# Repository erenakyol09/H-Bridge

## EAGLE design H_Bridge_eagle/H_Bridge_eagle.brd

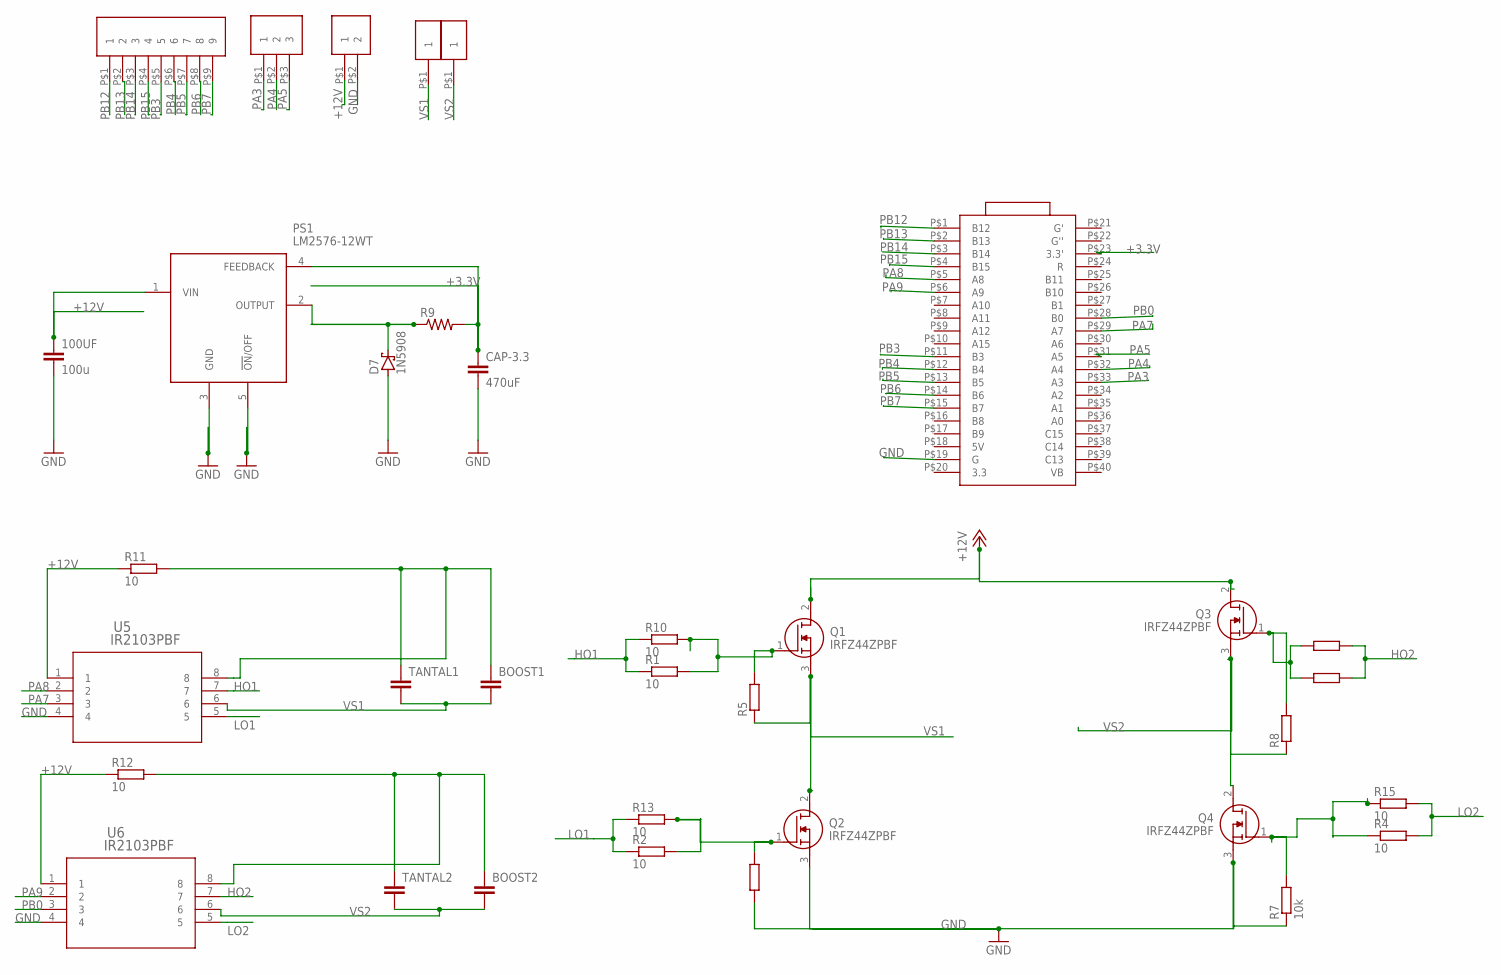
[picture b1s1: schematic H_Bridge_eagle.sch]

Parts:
100UF: 100u; C5B5
BOOST1, BOOST2: C-EU025-040X050; C025-040X050
CAP-3.3: 470uF; C050-075X075
D7: 1N5908; C4111-15
PS1: LM2576-12WT; TO170P470X1016X1900-5P
Q1, Q2, Q3, Q4: IRFZ44ZPBF; TO254P482X1016X2192-3P
R1, R2, R3, R4, R10, R11, R12, R13, R14, R15: 10; 0204/7
R5, R6, R7, R8: 10k; 0204/7
R9: R-US_VTA55; VTA55
TANTAL1, TANTAL2: C-EU025-024X044; C025-024X044
U5, U6: IR2103PBF; IC8_IR2103PBF_INF
U$1: BLUE_PILL_EA; BLUE_PILL_FOOT
U$2: HEADER_9; HEADER_9_FOOT
U$3: HEADER_3; HEADER_3_FOOT
U$4: HEADER_2; HEADER_2_FOOT
U$5, U$6: HEADER_1; HEADER_1_FOOT

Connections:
+3.3V: CAP-3.3.1, PS1.4 (FEEDBACK), R9.2, U$1.P$23 (3.3')
+12V: 100UF.1, PS1.1 (VIN), Q1.2 (D), Q3.2 (D), R11.1, R12.1, U5.1, U6.1, U$4.P$1 (1)
GND: 100UF.2, CAP-3.3.2, D7.A, PS1.3 (GND), PS1.5 (!ON!/OFF), Q2.3 (S), Q4.3 (S), R6.1, R7.1, U5.4, U6.4, U$1.P$19 (G), U$4.P$2 (2)
HO1: R1.1, R10.1, U5.7
HO2: R3.2, R14.2, U6.7
LO1: R2.1, R13.1, U5.5
LO2: R4.2, R15.2, U6.5
unnamed: BOOST2.1, R12.2, TANTAL2.1, U6.8
unnamed: BOOST1.1, R11.2, TANTAL1.1, U5.8
unnamed: D7.C, PS1.2 (OUTPUT), R9.1
unnamed: Q4.1 (G), R4.1, R7.2, R15.1
unnamed: Q3.1 (G), R3.1, R8.2, R14.1
unnamed: Q1.1 (G), R1.2, R5.2, R10.2
unnamed: Q2.1 (G), R2.2, R6.2, R13.2
PA3: U$1.P$33 (A3), U$3.P$1 (1)
PA4: U$1.P$32 (A4), U$3.P$2 (2)
PA5: U$1.P$31 (A5), U$3.P$3 (3)
PA7: U5.3, U$1.P$29 (A7)
PA8: U5.2, U$1.P$5 (A8)
PA9: U6.2, U$1.P$6 (A9)
PB0: U6.3, U$1.P$28 (B0)
PB3: U$1.P$11 (B3), U$2.P$5 (5)
PB4: U$1.P$12 (B4), U$2.P$6 (6)
PB5: U$1.P$13 (B5), U$2.P$7 (7)
PB6: U$1.P$14 (B6), U$2.P$8 (8)
PB7: U$1.P$15 (B7), U$2.P$9 (9)
PB12: U$1.P$1 (B12), U$2.P$1 (1)
PB13: U$1.P$2 (B13), U$2.P$2 (2)
PB14: U$1.P$3 (B14), U$2.P$3 (3)
PB15: U$1.P$4 (B15), U$2.P$4 (4)
VS1: BOOST1.2, Q1.3 (S), Q2.2 (D), R5.1, TANTAL1.2, U5.6, U$5.P$1
VS2: BOOST2.2, Q3.3 (S), Q4.2 (D), R8.1, TANTAL2.2, U6.6, U$6.P$1

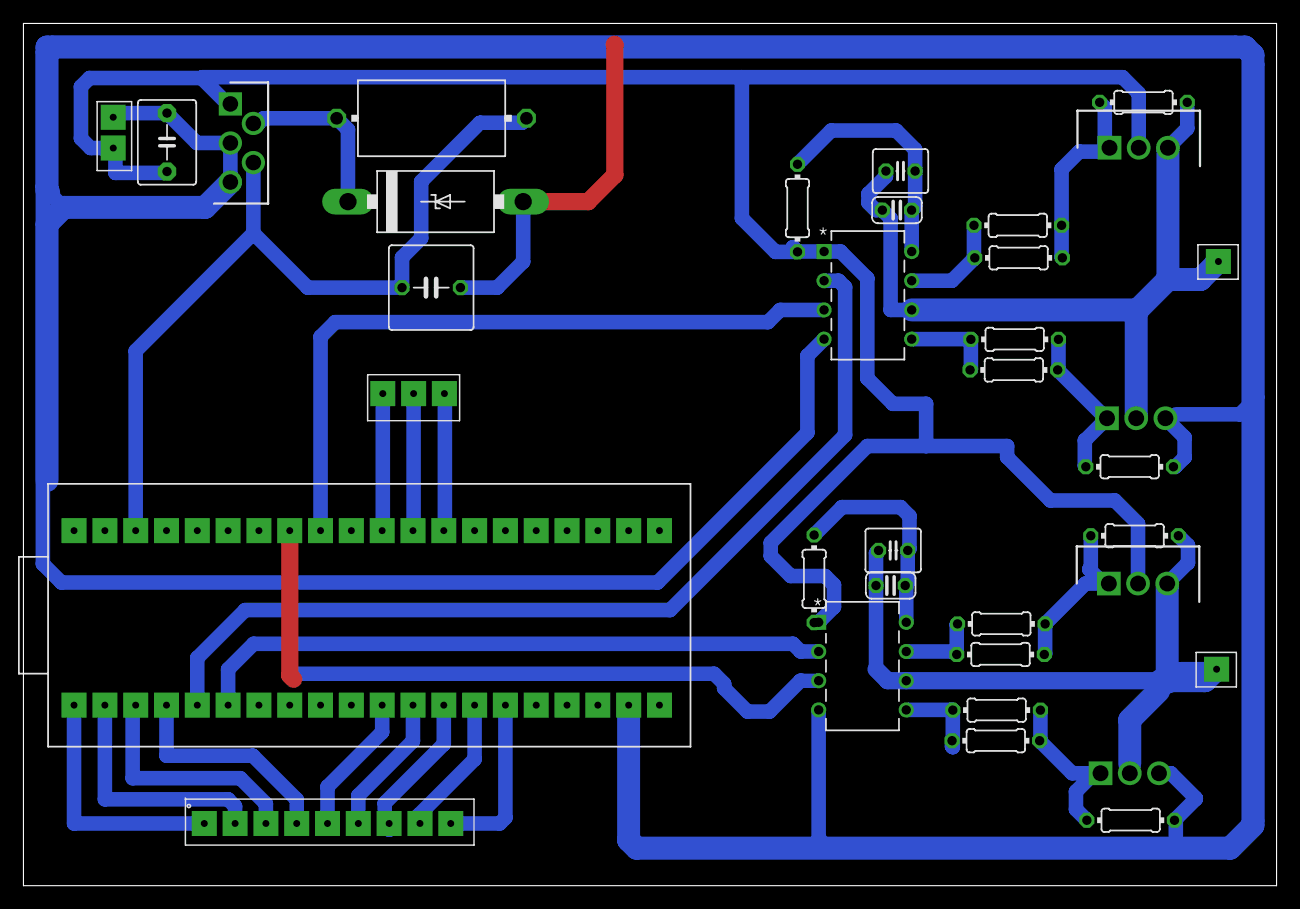
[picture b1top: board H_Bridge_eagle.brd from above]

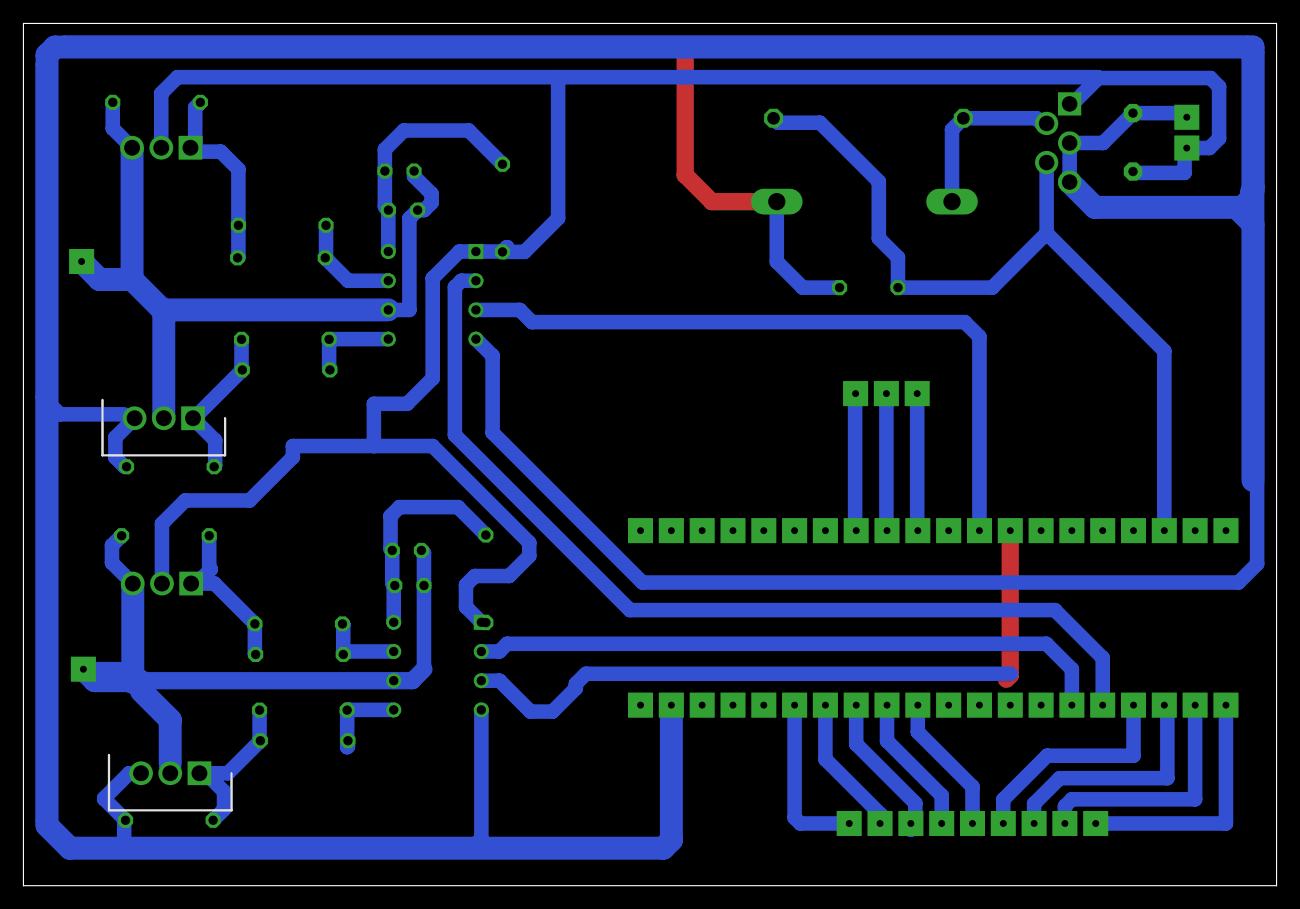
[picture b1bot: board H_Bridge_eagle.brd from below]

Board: 2 copper layers, 109.0 x 75.0 mm, 35 parts (2 on the bottom side), 32 nets.

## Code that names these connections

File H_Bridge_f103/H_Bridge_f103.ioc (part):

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Mcu.Name=STM32F103C(8-B)Tx
Mcu.Package=LQFP48
Mcu.UserName=STM32F103C8Tx
PA13.Mode=Serial_Wire
PA13.Signal=SYS_JTMS-SWDIO
PA14.Mode=Serial_Wire
PA14.Signal=SYS_JTCK-SWCLK
PA3.Signal=GPIO_Input
PA4.Signal=GPIO_Input
PA5.Signal=ADCx_IN5
PA7.Signal=S_TIM3_CH2
PA8.Signal=S_TIM1_CH1
PA9.Signal=S_TIM1_CH2
PB0.Signal=S_TIM3_CH3
PB12.GPIOParameters=GPIO_PuPd
PB12.GPIO_PuPd=GPIO_PULLUP
PB12.Signal=GPIO_Input
PB13.GPIOParameters=GPIO_PuPd
PB13.GPIO_PuPd=GPIO_PULLUP
PB13.Signal=GPIO_Input
PB14.GPIOParameters=GPIO_PuPd
PB14.GPIO_PuPd=GPIO_PULLUP
PB14.Signal=GPIO_Input
PB15.GPIOParameters=GPIO_PuPd
PB15.GPIO_PuPd=GPIO_PULLUP
PB15.Signal=GPIO_Input
PB3.Signal=GPIO_Output
PB4.Signal=GPIO_Output
PB5.Signal=GPIO_Output
PB6.Signal=GPIO_Output
PB7.Signal=GPIO_Output
PC13-TAMPER-RTC.Signal=GPIO_Output
PD0-OSC_IN.Mode=HSE-External-Oscillator
PD0-OSC_IN.Signal=RCC_OSC_IN
PD1-OSC_OUT.Mode=HSE-External-Oscillator
PD1-OSC_OUT.Signal=RCC_OSC_OUT
board=custom

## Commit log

2020-07-20 h_bridge version1
2020-07-20 pid,current,encoder

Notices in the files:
parts and their libraries:
COPYRIGHT: Copyright (C) 2018 Accelerated Designs. All rights reserved
